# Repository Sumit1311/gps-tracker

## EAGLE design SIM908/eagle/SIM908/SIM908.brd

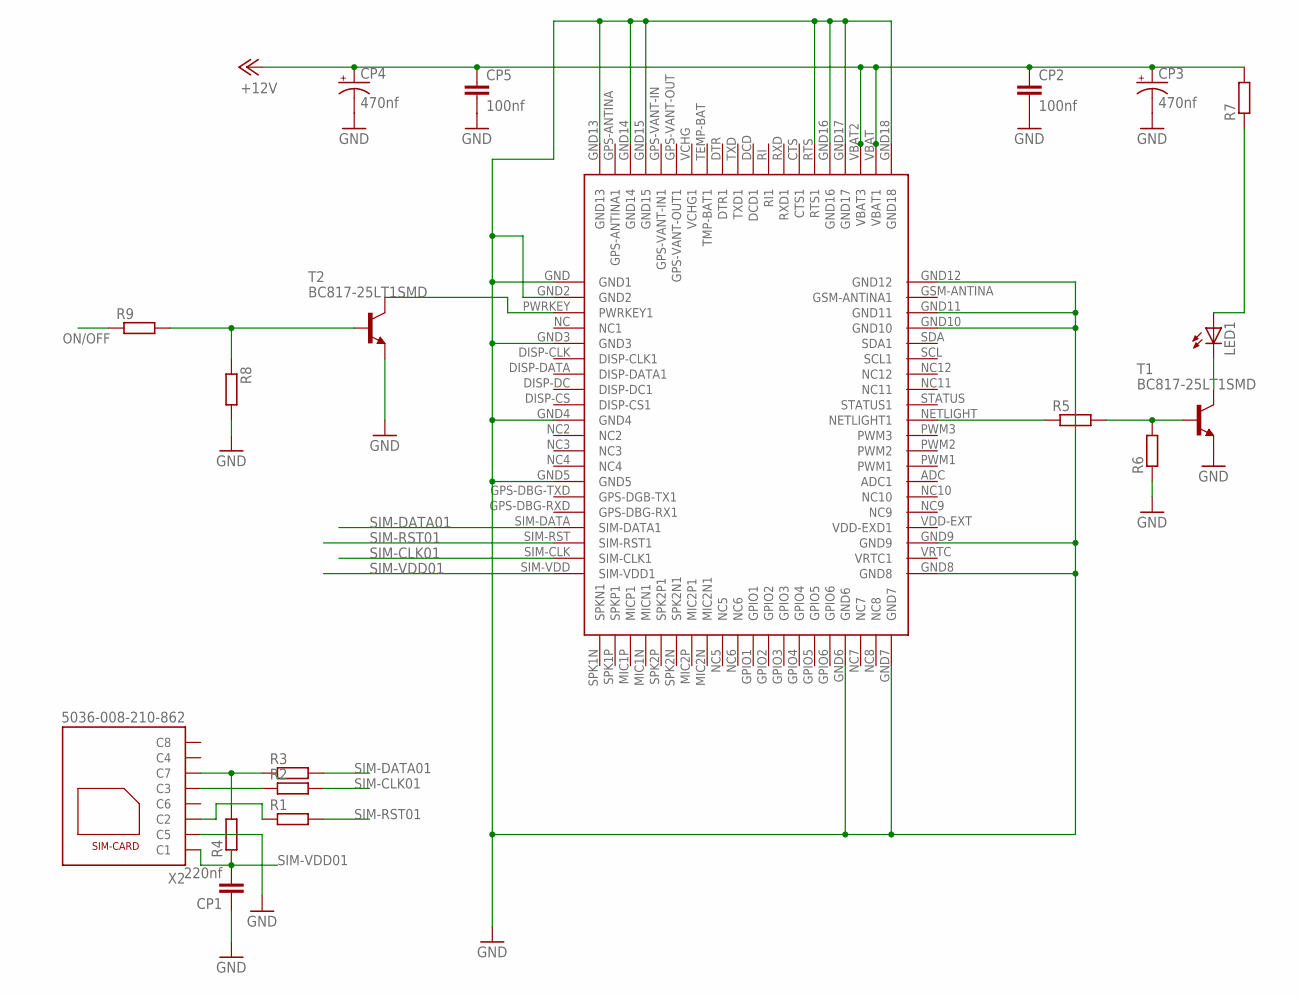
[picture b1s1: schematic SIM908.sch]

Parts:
CP1: 220nf; C15B9
CP2, CP5: 100nf; C15B9
CP3, CP4: 470nf; 153CLV-0807
LED1: LED_E; LED_1206
R1, R2, R3, R4, R5, R6, R7, R8, R9: R-EU_0207/12; 0207/12
T1, T2: BC817-25LT1SMD; SOT23-BEC
U$2: SIM908
X2: 5036-008-210-862; 5036_008_210_862

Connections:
+12V: CP2.1, CP3.+, CP4.+, CP5.1, R7.2, U$2.VBAT (VBAT1), U$2.VBAT2 (VBAT3)
GND: CP1.1, CP2.2, CP3.-, CP4.-, CP5.2, R6.1, R8.2, T1.E, T2.E, U$2.GND (GND1), U$2.GND2, U$2.GND3, U$2.GND4, U$2.GND5, U$2.GND6, U$2.GND7, U$2.GND8, U$2.GND9, U$2.GND10, U$2.GND11, U$2.GND12, U$2.GND13, U$2.GND14, U$2.GND15, U$2.GND16, U$2.GND17, U$2.GND18, U$2.RTS (RTS1), X2.C5
unnamed: R2.1, X2.C3
unnamed: R3.1, R4.2, X2.C7
unnamed: R1.1, X2.C2
unnamed: T2.C, U$2.PWRKEY (PWRKEY1)
unnamed: R8.1, R9.2, T2.B
unnamed: R5.2, R6.2, T1.B
unnamed: LED1.C, T1.C
unnamed: LED1.A, R7.1
unnamed: R5.1, U$2.NETLIGHT (NETLIGHT1)
ON/OFF: R9.1
SIM-CLK01: R2.2, U$2.SIM-CLK (SIM-CLK1)
SIM-DATA01: R3.2, U$2.SIM-DATA (SIM-DATA1)
SIM-RST01: R1.2, U$2.SIM-RST (SIM-RST1)
SIM-VDD01: CP1.2, R4.1, U$2.SIM-VDD (SIM-VDD1), X2.C1

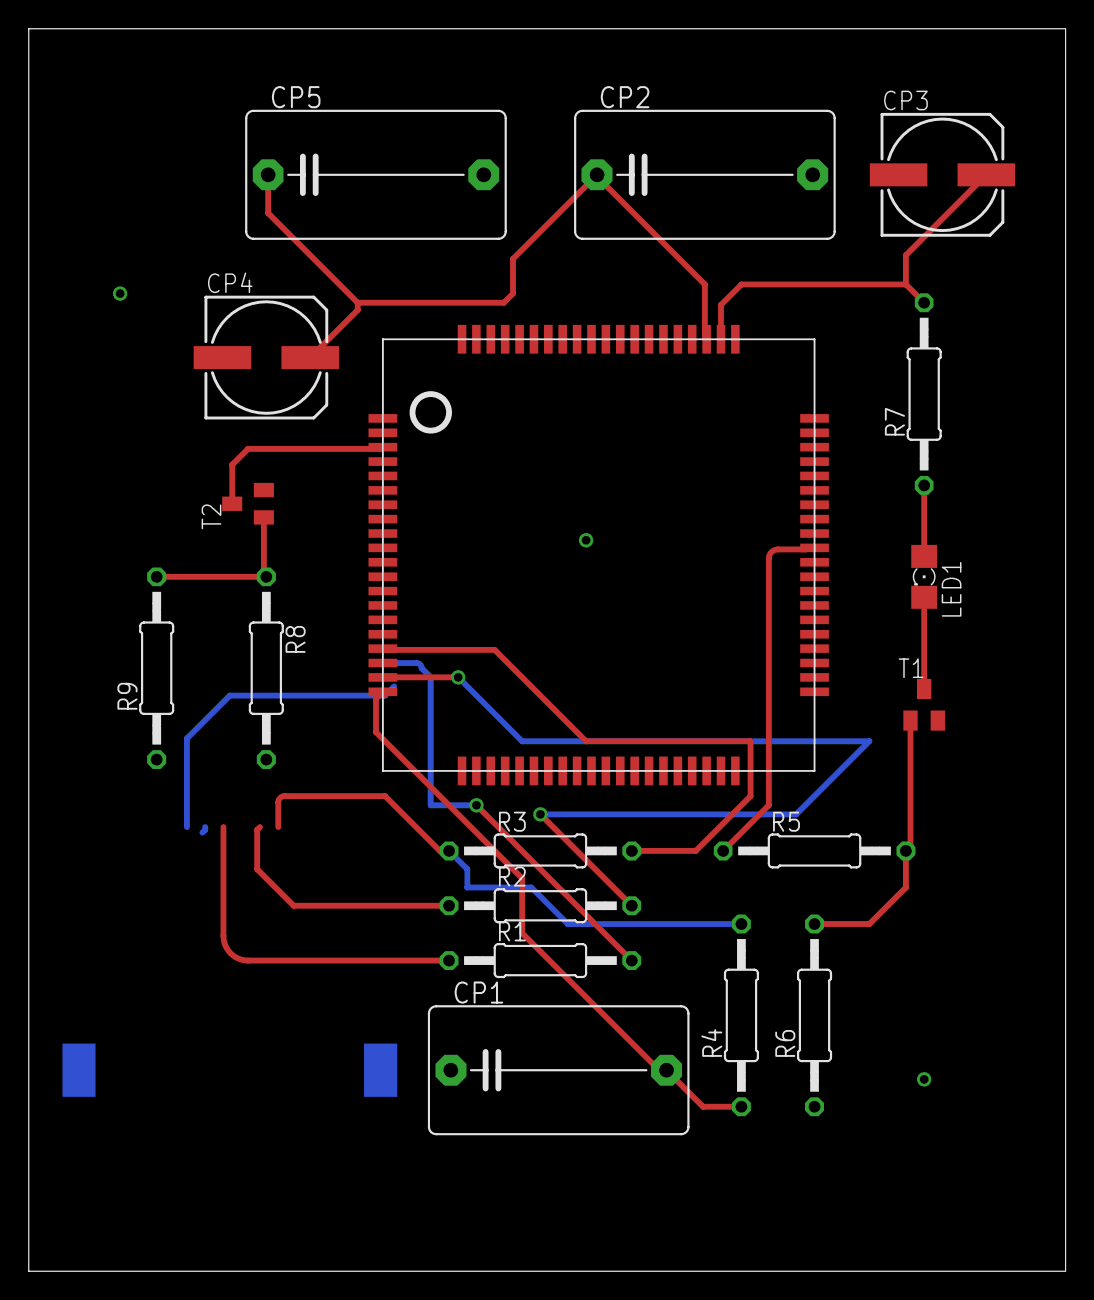
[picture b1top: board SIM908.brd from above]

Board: 2 copper layers, 72.1 x 86.4 mm, 19 parts (1 on the bottom side), 15 nets.

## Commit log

2016-05-15 added client side code
2016-05-16 added database support
2016-07-13 added working code
2016-07-14 added code to run seperate containers using docker : tested and verified
2017-01-11 adding eagle and gerber files
2017-01-13 renamed folde rto proper names
